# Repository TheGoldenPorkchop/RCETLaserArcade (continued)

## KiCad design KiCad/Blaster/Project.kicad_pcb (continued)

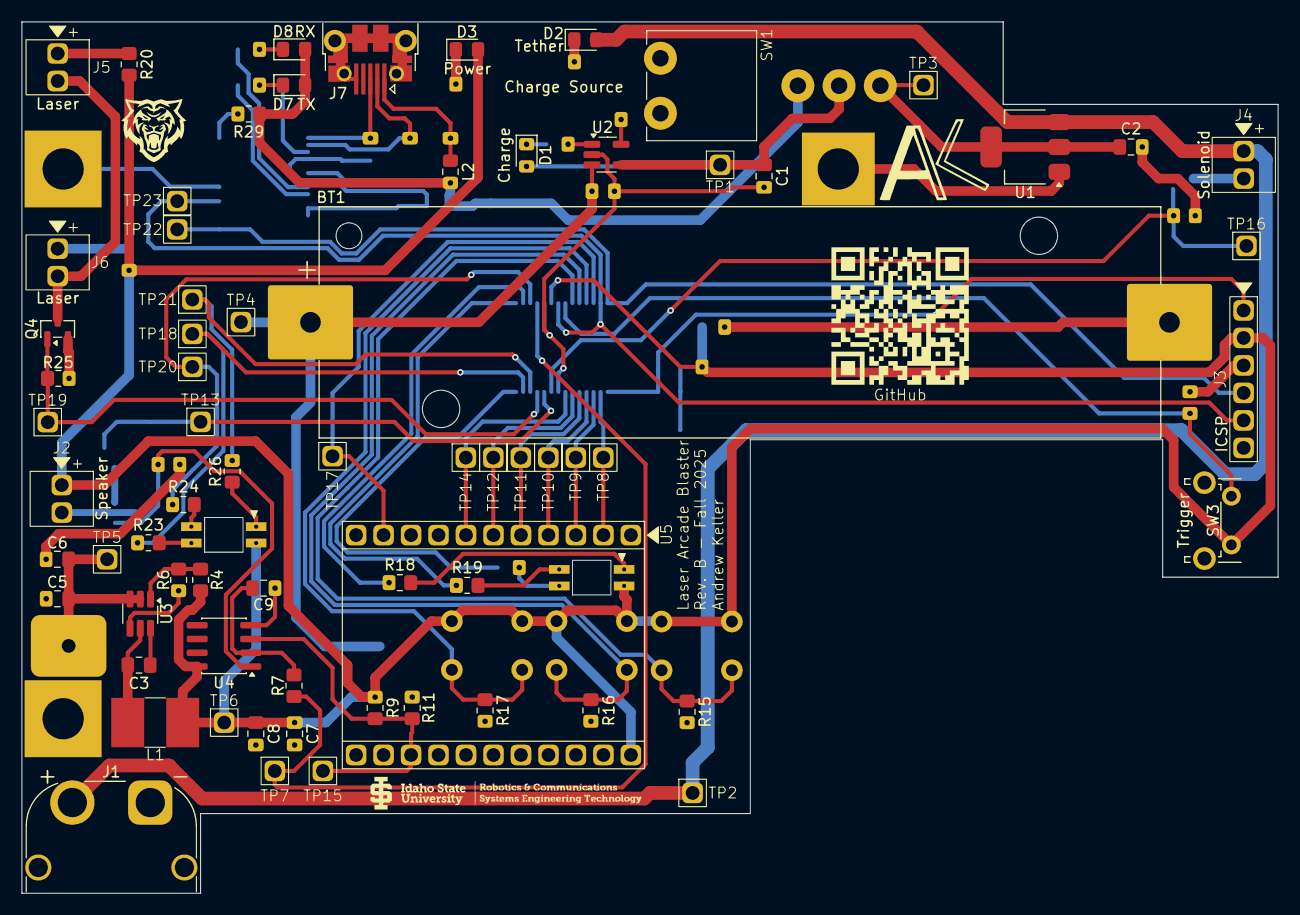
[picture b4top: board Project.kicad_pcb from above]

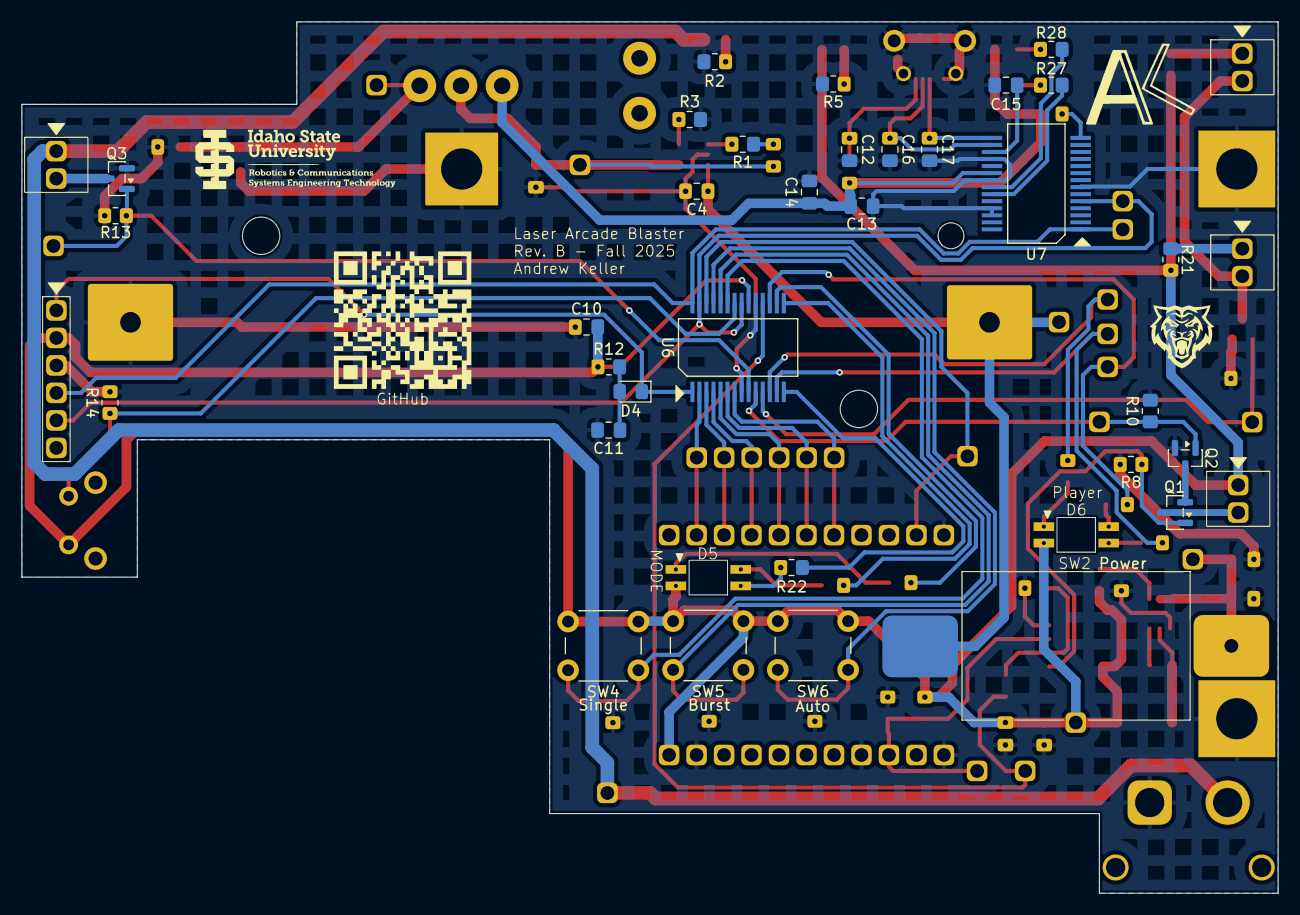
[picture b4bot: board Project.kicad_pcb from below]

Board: 2 copper layers, 116.0 x 80.5 mm, 104 parts (34 on the bottom side), 65 nets.

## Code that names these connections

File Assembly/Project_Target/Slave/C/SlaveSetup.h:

/*
   Filename:        BlasterSetup.h                                                          
   Date:            November 18, 2025                                                    
   File Version:    1                                                               
   Author:          Andrew Keller                                                       
   Company:         Idaho State University					    
   Description:     Laser Arcade Blaster Setup Header File
*/

// This is a guard condition so that contents of this file are not included
// more than once.  
#ifndef BLASTER_SETUP
#define	BLASTER_SETUP

#include <xc.h> // include processor files - each processor file is guarded.  

//define oscillation frequency
#define _XTAL_FREQ 8000000 //Fosc of 8MHz

//define PORTA pin names
#define AudioTRIG0 PORTAbits.RA0
#define AudioTRIG1 PORTAbits.RA1
#define AudioTRIG2 PORTAbits.RA2
#define AudioTRIG3 PORTAbits.RA3
#define AudioTRIG4 PORTAbits.RA4
#define AudioTRIG5 PORTAbits.RA5
#define AudioEnable PORTAbits.RA6
#define Solenoid PORTAbits.RA7

//define PORTB interrupt flag names
#define TriggerButtonFlag IOCBFbits.IOCBF1
#define TriggerButton PORTBbits.RB1
#define SingleButtonFlag IOCBFbits.IOCBF2
#define BurstButtonFlag IOCBFbits.IOCBF3
#define AutoButtonFlag IOCBFbits.IOCBF4
#define AudioActivity PORTBbits.RB5

//define PORTC pin names
#define ModeBlue PORTCbits.RC5
#define ModeRed PORTCbits.RC3
#define ModeGreen PORTCbits.RC4

//define RAM addresses
#define RAMPlayerNumber 0x20
#define RAMPlayerRed 0x21
#define RAMPlayerGreen 0x22
#define RAMPlayerBlue 0x23
#define RAMMode 0x24

//define EEPROM addresses
#define EEPROMPlayerNumber 0x00
#define EEPROMPlayerRed 0x01
#define EEPROMPlayerGreen 0x02
#define EEPROMPlayerBlue 0x03

//Function Prototypes
void Setup_ConfigureOscillator(void);
void Setup_ConfigureOptions(void);
void Setup_ConfigurePinFunctions(void);
void Setup_ConfigurePortA(void);
void Setup_ConfigurePortB(void);
void Setup_ConfigurePortC(void);
void Setup_ConfigureI2C(void);
void Setup_ConfigureAudio(unsigned char PlayerNum);
void Setup_ConfigureInterrupts(void);

#endif	/* Blaster_SETUP */

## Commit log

2025-10-28 Ignore KiCad auto save file
2025-10-28 Add servo and stepper outputs to slave schematic and increase number of power pins at I2C headers
2025-10-28 Print updated slave schematic to PDF
2025-11-03 Add MCP73831 Lipo charge IC datasheet
2025-11-03 Blaster schematic update PIC, solenoid, and FX Mini
2025-11-04 Updated Blaster Microcontroller Schematic
2025-11-04 Add blaster MOSFET datasheet
2025-11-04 Blaster Power and Communications schematic updates. Add Revision B schematic
2025-11-04 Init Target Jumper
2025-11-04 Target Jumper Schematics
2025-11-05 Complete Target Jumper PCB
2025-11-06 Rev B Target Slave PCB design
2025-11-06 Plot Target Slave Gerbers
2025-11-06 Plot Target Jumper PCB and Schematic
2025-11-07 Re-export gerbers
2025-11-12 Assign blaster footprints, Create Blaster PCB Outline
2025-11-12 Assign blaster PCB Footprints
2025-11-12 Place major components on PCB
2025-11-14 Complete Blaster PCB layout and traces
2025-11-14 Update blaster schematic date and print
2025-11-14 Complete Blaster PCB Export
2025-11-14 Move Master Rev A files to Rev A folder
2025-11-14 Add PIC Datasheet
2025-11-17 Completed Target Master Rev. B PCB
2025-11-17 Completed Target Master PCB, export gerbers and views
2025-11-17 Export Blaster 3D Image, Minor text changes on Master PCB
2025-11-17 Export Target Slave PCB Images, update date
2025-11-17 Add WS2812B LED Protocol include file
2025-11-18 Move existing code to Rev A. Init Rev. B
2025-11-18 Basic PIC setup
2025-11-18 Player LED PWM configuration
2025-11-19 Add EEPROM read and write
2025-11-19 Add Laser Configuration
2025-11-19 Change fire mode, layout interrupt on change ISR
2025-11-19 Add IR transmit blaster fire for single, burst, and auto modes
2025-11-20 Solenoid activation with fire, move blaster fire into subroutine
2025-11-20 Added UART Controller
2025-11-21 -Added Fields/State section to use for the device verification process later -Added some custom events to be used later -Reformatted comments (Headers & process blocks) -Started creating the Connect 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
2025-12-02 -Added Device Verfication
2025-12-05 updated master code test 1
2025-12-07 Exporting pcb images
2025-12-07 Add DMG3402L MOSFET datasheet to references
2025-12-07 Blaster UART commands, aligning audio with solenoid
2025-12-08 Sends a to UART after a successfull WRITE_I2C AND WRITE_COLOR_I2C command
2025-12-09 Trying to get the slave to work
2025-12-10 Slave responds to UART and I2C
2025-12-10 Reduce LED flash speed when hit
2025-12-10 started Lightning game VB UI
2025-12-10 there was a page turn apparently. Added one NOP and the I2C Read now sends the data to UART
2025-12-10 Updated slave code
2025-12-11 Read settings UART command, start of I2C color change command
2025-12-11 edited the comment that skipped the line, and removed the NOP
2025-12-11 Revert "Read settings UART command, start of I2C color change command"
    This reverts commit f1f14a76106aaaaaa9ff06ae6aa145f69a44b6fe.
2025-12-11 Read settings command
2025-12-12 Assembly: added a way to clear timeout flag. VB: added a player class to update colors and small ui development
2025-12-12 -Added comments & Procedure for data parsing
2025-12-14 Updated servo positions, hit and enable indicators, not hit while disabled, file headers
2025-12-15 Remove lines in enable/disable target subroutines to activate correct number of LEDs
2025-12-15 Startup form design and code
2025-12-15 Menu Navigation Logic, refresh available COM ports
2025-12-15 Add PlayerColors class
2025-12-15 UI is a bit scuffed but done
2025-12-15 Blaster Configuration
2025-12-15 Move the player class into the class folder
2025-12-15 Slave configuration form gui design
2025-12-16 Slave Configuration form
2025-12-16 Updated AboutForm information
2025-12-16 Add icons
2026-03-10 Final Commit
2026-03-10 Day one Test. Changed the start up form to be the StartupForm
2026-03-31 Added Game Picker and Testing Form
2026-04-01 Added TicTacToe Functionality
2026-04-06 Added Data Parsing, Events, and Handler to the UARTController.
2026-04-06 Removed GIE
2026-04-06 Tic Tac Toe Kinda works with the blaster. A tad bit inconsistent
2026-04-06 TicTacToe Works a bit better (UART Recieve breaks sometimes)
2026-04-10 Added TicTacToe and Memory. Needs UART Controller Fixes.
